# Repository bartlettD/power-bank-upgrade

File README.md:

# Power Bank Upgrade

A replacement PCB for a cheap single cell power bank.

Designed with KiCad 5.0.2

PDF Schematics, Gerbers and Images are available in the "Docs" directory.

<p float="center">

</p>

## Introduction

This is a single cell, Li-Ion USB Power bank based around an Monolithic Power 
Solutions MP2632B IC.

The board was designed to be broadly compatible with the plastics from a common
model of power bank available from Pound shops except with a few extra features.

## Features

* 3000 mAh LG HG2 Cell. 250% more capacity!
* State of Charge LED indicator.
* Faster Charge and Discharge Currents. (3A)
* Thermistor Thermal Regulation and Shutdown.
* Will actually charge a modern smartphone.

## Licence
The project is licenced under the MIT licence.

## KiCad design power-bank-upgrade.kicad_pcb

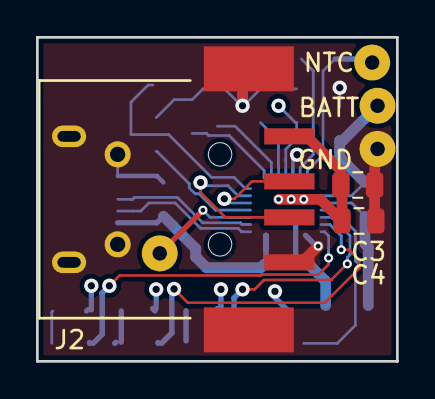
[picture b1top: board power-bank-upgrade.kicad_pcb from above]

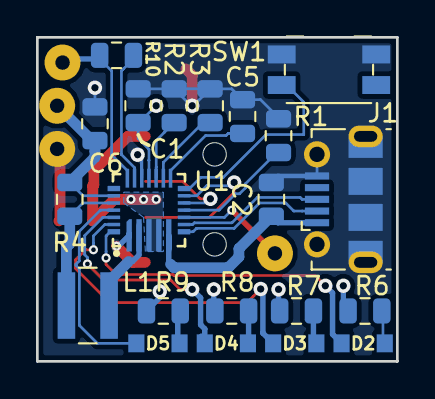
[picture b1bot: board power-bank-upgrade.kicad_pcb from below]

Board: 4 copper layers, 20.0 x 18.0 mm, 28 parts (21 on the bottom side), 27 nets.

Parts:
BATT: Conn_01x01_Female; SolderWirePad_1x01_Drill0.8mm
C1: 100nF; C_0805_2012Metric
C2, C3, C4: 22uF; C_0805_2012Metric
C5, C6: C; C_0805_2012Metric
D2, D3, D4, D5: LED; APA2107
GND: Conn_01x01_Female; SolderWirePad_1x01_Drill0.8mm
J1: USB_B_Micro; USB_Micro-B_Molex-105017-0001
J2: USB_A; USB_A_Samtec_USB-A-S-F-B-SM2.kicad_mod
J6: Conn_01x01_Female; SolderWirePad_1x01_Drill0.8mm
L1: 2.2uH; L_Wuerth_MAPI-4020
NTC: Conn_01x01_Female; SolderWirePad_1x01_Drill0.8mm
R1: 13.3k; R_0805_2012Metric
R2, R3: 49.9k; R_0805_2012Metric
R4: 10m; R_0805_2012Metric
R6, R7, R8, R9: 210; R_0805_2012Metric
R10: R; R_0805_2012Metric
SW1: SW_Push; Panasonic_EVQPUJ_EVQPUA
U1: MP2632B; MPS_QFN_26_4x4mm_P0.4mm

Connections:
/NTC+: NTC.1, R10.1, U1.19
/VBATT: BATT.1, C6.1, R4.1, U1.21
/VNTC: R10.2, U1.18
GNDA: C1.2, C2.2, C3.2, C4.2, C5.2, C6.2, GND.1, J1.5, J1.6, J2.4, J2.5, R1.2, R2.2, R3.2, SW1.1, U1.1, U1.17
unnamed: C2.1, J1.1, U1.5
unnamed: C3.1, C4.1, J2.1, U1.3, U1.4
unnamed: C5.1, U1.13
unnamed: D2.1, U1.26
unnamed: D2.2, R6.2
unnamed: D3.1, U1.25
unnamed: D3.2, R7.2
unnamed: D4.1, U1.24
unnamed: D4.2, R8.2
unnamed: D5.1, U1.23
unnamed: D5.2, R9.2
unnamed: J1.2, U1.6
unnamed: J1.3, U1.7
unnamed: J2.2, U1.10
unnamed: J2.3, U1.11
unnamed: J6.1, U1.8
unnamed: L1.1, U1.2
unnamed: L1.2, R4.2, U1.22
unnamed: R1.1, U1.9
unnamed: R2.1, U1.15
unnamed: R3.1, U1.14
unnamed: SW1.2, U1.12
VCC: C1.1, R6.1, R7.1, R8.1, R9.1, U1.16

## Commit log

2018-12-06 Created initial project files. Creating MPS MP2632B symbol
2018-12-06 Added pin no's to symbol
2018-12-06 Started schematic work
2018-12-06 Started building footprint for MPS battery IC
2018-12-09 Created PCB, started routing. Saving work to try nighly build
2018-12-09 Abandoning Kicad. Uphill battle
2018-12-09 sym-lib-table
2018-12-16 Added Samtec USB Type A portm started routing
2019-01-12 Completed routing for v1. Added fp-info-cache to .gitignore
2019-02-18 Updated cap values. Increased LED resistor value to reduce current draw. Added NTC thermistor
2019-02-18 Updated README with some project information.
2019-05-05 Adding Documentation
    Adding PDF Schematics, Gerbers, 3D Model and Renders
2019-05-05 Adding Images To README
2019-05-06 Correct Spelling In README
    Fixes #1
